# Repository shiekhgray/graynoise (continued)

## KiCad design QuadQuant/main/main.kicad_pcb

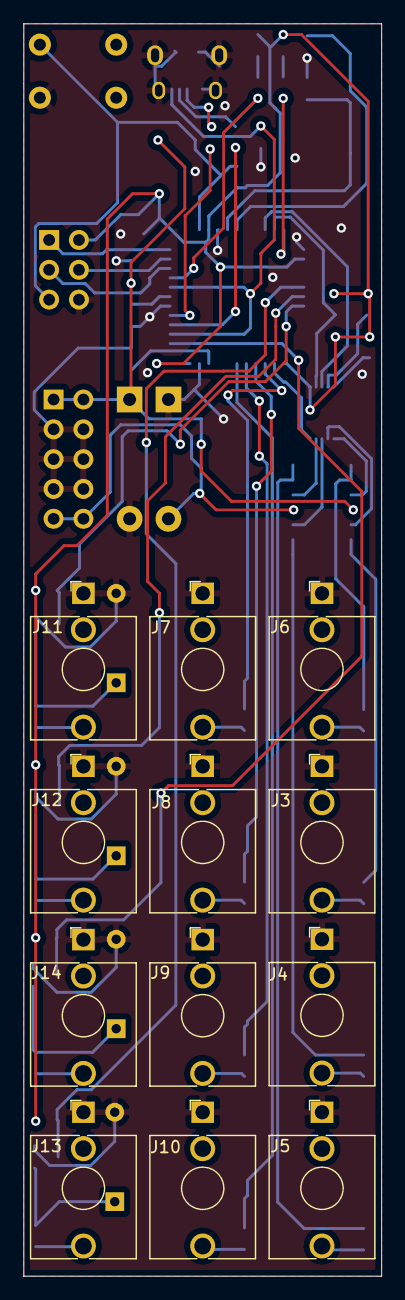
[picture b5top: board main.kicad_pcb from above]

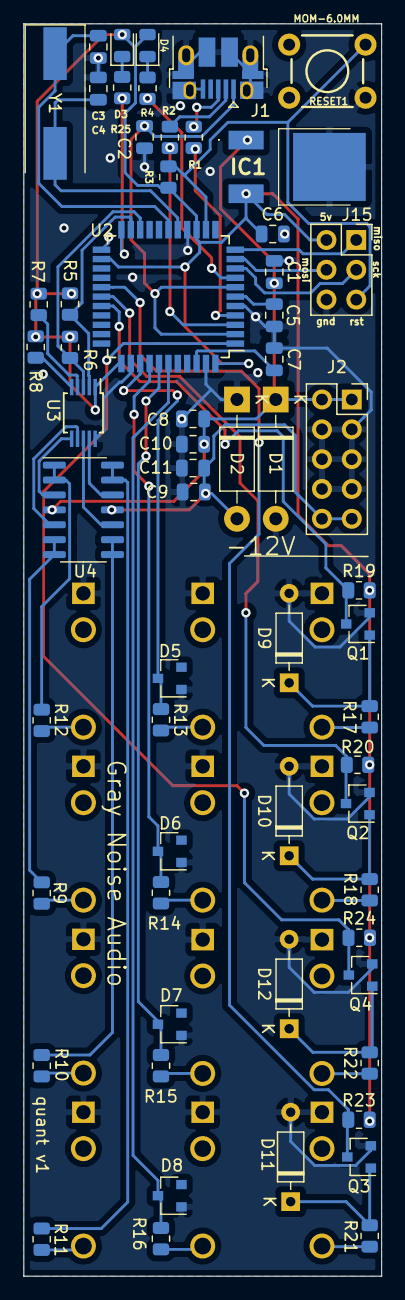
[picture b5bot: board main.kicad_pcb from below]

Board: 2 copper layers, 30.5 x 106.7 mm, 73 parts (61 on the bottom side), 57 nets.

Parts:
C1, C6, C7, C10, C11: 100n; C_0805_2012Metric
C2, C5: 1u; C_0805_2012Metric
C3, C4: 22p; C_0805_2012Metric
C8, C9: 10u; C_0805_2012Metric
D1, D2: 1N4001; D_DO-41_SOD81_P10.16mm_Horizontal
D3: LED_Green; LED_0805_2012Metric
D4: LED_Yellow; LED_0805_2012Metric
D5, D6, D7, D8: D_Zener_5v; D_SOT-23_ANK
D9, D10, D11, D12: 1N4148; D_DO-35_SOD27_P7.62mm_Horizontal
IC1: MC7805CDTRKG; MJD1221G
J1: USB_B_Mini; USB_Micro-B_Amphenol_10103594-0001LF_Horizontal
J2: Conn_02x05_Odd_Even; PinSocket_2x05_P2.54mm_Vertical
J3: OUT2; Jack_3.5mm_QingPu_WQP-PJ398SM_Vertical_CircularHoles
J4: OUT3; Jack_3.5mm_QingPu_WQP-PJ398SM_Vertical_CircularHoles
J5: OUT4; Jack_3.5mm_QingPu_WQP-PJ398SM_Vertical_CircularHoles
J6: OUT1; Jack_3.5mm_QingPu_WQP-PJ398SM_Vertical_CircularHoles
J7: CV1; Jack_3.5mm_QingPu_WQP-PJ398SM_Vertical_CircularHoles
J8: CV2; Jack_3.5mm_QingPu_WQP-PJ398SM_Vertical_CircularHoles
J9: CV3; Jack_3.5mm_QingPu_WQP-PJ398SM_Vertical_CircularHoles
J10: CV4; Jack_3.5mm_QingPu_WQP-PJ398SM_Vertical_CircularHoles
J11: Trig1; Jack_3.5mm_QingPu_WQP-PJ398SM_Vertical_CircularHoles
J12: Trig2; Jack_3.5mm_QingPu_WQP-PJ398SM_Vertical_CircularHoles
J13: Trig4; Jack_3.5mm_QingPu_WQP-PJ398SM_Vertical_CircularHoles
J14: Trig3; Jack_3.5mm_QingPu_WQP-PJ398SM_Vertical_CircularHoles
J15: Conn_02x03_Odd_Even; PinSocket_2x03_P2.54mm_Vertical
Q1, Q2, Q3, Q4: MMBT3904; SOT-23
R1, R2: 22; R_0805_2012Metric
R3: 10K; R_0805_2012Metric
R4, R9, R10, R11, R12, R25: 1K; R_0805_2012Metric
R5, R6, R7, R8, R13, R14, R15, R16, R17, R18, R19, R20, R21, R22, R23, R24: 100K; R_0805_2012Metric
RESET1: MOM-6.0MM; TACTILE_SWITCH_PTH_6.0MM
U2: ATmega32U4-AU; TQFP-44_10x10mm_P0.8mm
U3: MCP4728; MSOP-10_3x3mm_P0.5mm
U4: TL074; SOIC-14_3.9x8.7mm_P1.27mm
Y1: Crystal16mhz; Crystal_SMD_HC49-SD

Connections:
+5V: C6.1, D3.2, D4.2, IC1.3, J15.2, R3.1, R5.1, R6.1, R7.1, R8.1, R19.2, R20.2, R23.2, R24.2, U2.14, U2.24, U2.34, U2.44, U3.1
+12V: C1.2, C8.2, C10.2, D1.1, IC1.1, J2.1, J2.2, U4.4
-12V: C9.1, C11.1, D2.2, J2.9, J2.10, U4.11
CVA: D5.1, R13.1, U2.36
CVB: D6.1, R14.1, U2.37
CVC: D7.1, R15.1, U2.38
CVD: D8.1, R16.1, U2.39
GND: C1.1, C2.1, C3.2, C4.2, C5.1, C6.2, C7.1, C8.1, C9.2, C10.1, C11.2, D1.2, D2.1, D5.2, D6.2, D7.2, D8.2, D9.2, D10.2, D11.2, D12.2, IC1.2, J1.5, J1.6, J2.3, J2.4, J2.5, J2.6, J2.7, J2.8, J3.S, J4.S, J5.S, J6.S, J7.S, J8.S, J9.S, J10.S, J11.S, J12.S, J13.S, J14.S, J15.6, Q1.2, Q2.2, Q3.2, Q4.2, RESET1.1, U2.5, U2.15, U2.23, U2.35, U2.43, U3.10
LDAC: R7.2, U3.4
MISO: J15.1, U2.11
MOSI: J15.4, U2.10
unnamed: C3.1, U2.17, Y1.1
unnamed: C4.1, U2.16, Y1.2
unnamed: C5.2, U2.6
unnamed: C7.2, U2.42
unnamed: D3.1, R25.1
unnamed: D4.1, R4.1
unnamed: D9.1, Q1.1, R17.1
unnamed: D10.1, Q2.1, R18.1
unnamed: D11.1, Q3.1, R21.1
unnamed: D12.1, Q4.1, R22.1
unnamed: J1.2, R2.2
unnamed: J1.3, R1.2
unnamed: J3.T, R9.1
unnamed: J4.T, R10.1
unnamed: J5.T, R11.1
unnamed: J6.T, R12.1
unnamed: J7.T, R13.2
unnamed: J8.T, R14.2
unnamed: J9.T, R15.2
unnamed: J10.T, R16.2
unnamed: J11.T, R17.2
unnamed: J12.T, R18.2
unnamed: J13.T, R21.2
unnamed: J14.T, R22.2
unnamed: R1.1, U2.4
unnamed: R2.1, U2.3
unnamed: R4.2, U2.8
unnamed: R9.2, U4.6, U4.7
unnamed: R10.2, U4.8, U4.9
unnamed: R11.2, U4.13, U4.14
unnamed: R12.2, U4.1, U4.2
unnamed: R25.2, U2.22
RDY: R8.2, U3.5
RST: J15.5, R3.2, RESET1.3, U2.13
SCK: J15.3, U2.9
SCL: R5.2, U2.21, U3.2
SDA: R6.2, U2.20, U3.3
Trigger1: Q1.3, R19.1, U2.29
Trigger2: Q2.3, R20.1, U2.28
Trigger3: Q4.3, R24.1, U2.1
Trigger4: Q3.3, R23.1, U2.27
VOUTA: U3.6, U4.3
VOUTB: U3.7, U4.5
VOUTC: U3.8, U4.10
VOUTD: U3.9, U4.12
vbus: C2.2, J1.1, U2.2, U2.7

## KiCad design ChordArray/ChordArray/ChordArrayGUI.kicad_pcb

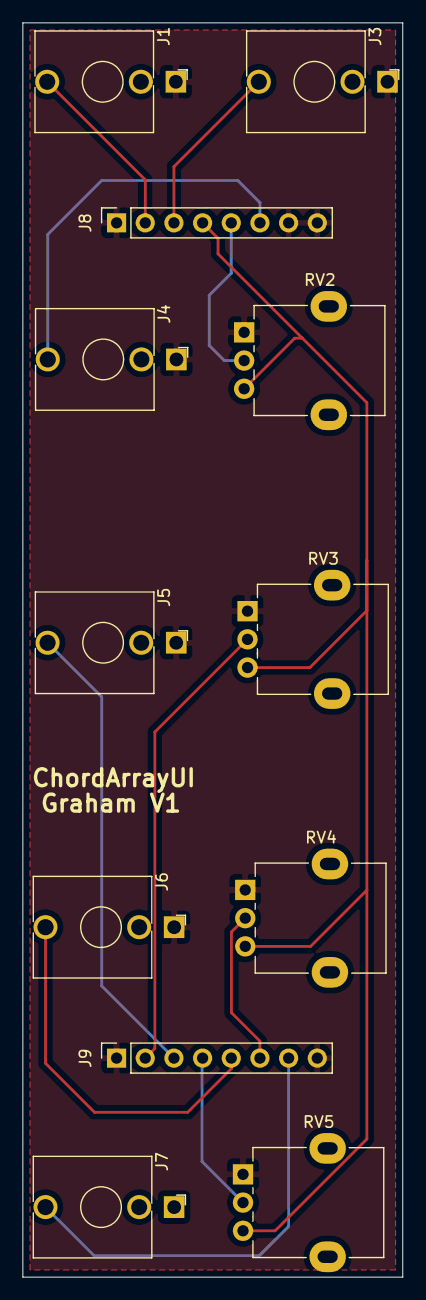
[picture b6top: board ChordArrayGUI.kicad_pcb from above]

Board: 2 copper layers, 33.7 x 111.1 mm, 12 parts (0 on the bottom side), 12 nets.

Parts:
J1: CV_IN; Jack_3.5mm_QingPu_WQP-PJ398SM_Vertical_CircularHoles
J3: BUFFERED_OUT; Jack_3.5mm_QingPu_WQP-PJ398SM_Vertical_CircularHoles
J4: OFFSET1; Jack_3.5mm_QingPu_WQP-PJ398SM_Vertical_CircularHoles
J5: OFFSET2; Jack_3.5mm_QingPu_WQP-PJ398SM_Vertical_CircularHoles
J6: OFFSET3; Jack_3.5mm_QingPu_WQP-PJ398SM_Vertical_CircularHoles
J7: OFFSET4; Jack_3.5mm_QingPu_WQP-PJ398SM_Vertical_CircularHoles
J8, J9: Conn_01x08_Male; PinSocket_1x08_P2.54mm_Vertical
RV2, RV3, RV4, RV5: 100K; Potentiometer_Alpha_RD901F-40-00D_Single_Vertical

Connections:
1V: J8.4, RV2.3, RV3.3, RV4.3, RV5.3
BUFFOUT: J3.T, J8.3
CVIN: J1.T, J8.2
GND: J1.S, J3.S, J4.S, J5.S, J6.S, J8.1, J8.7, J8.8, J9.1, J9.8, RV2.1, RV3.1, RV4.1, RV5.1
OFFP1: J8.5, RV2.2
OFFP2: J9.2, RV3.2
OFFP3: J9.4, RV5.2
OFFP4: J9.6, RV4.2
OFFS1: J4.T, J8.6
OFFS2: J5.T, J9.3
OFFS3: J6.T, J9.5
OFFS4: J7.T, J9.7

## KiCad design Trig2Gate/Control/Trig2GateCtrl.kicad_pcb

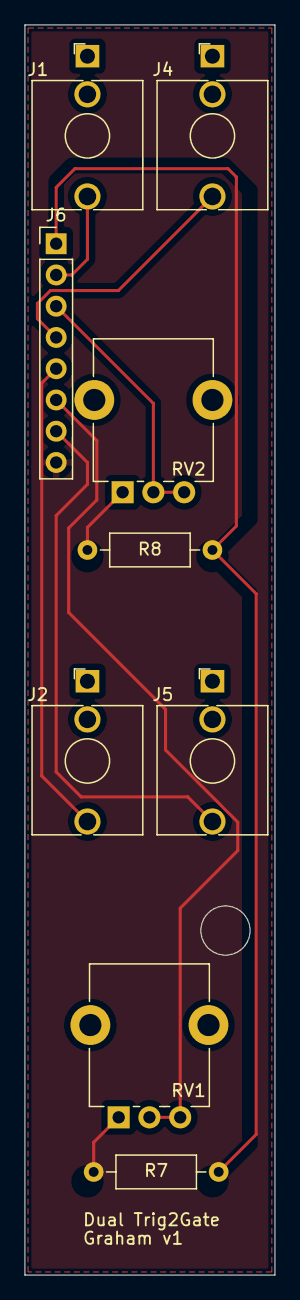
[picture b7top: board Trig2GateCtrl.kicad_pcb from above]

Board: 2 copper layers, 20.3 x 101.6 mm, 9 parts (0 on the bottom side), 9 nets.

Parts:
J1, J2, J4, J5: AudioJack2_Ground; Jack_3.5mm_QingPu_WQP-PJ398SM_Vertical_CircularHoles
J6: Conn_01x08_Male; PinHeader_1x08_P2.54mm_Vertical
R7, R8: 2K2; R_Axial_DIN0207_L6.3mm_D2.5mm_P10.16mm_Horizontal
RV1, RV2: 1M; Potentiometer_Alpha_RD901F-40-00D_Single_Vertical_CircularH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

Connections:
+12V: J6.1, R7.1, R8.1
G1: J4.T, J6.4
G2: J5.T, J6.7
unnamed: R7.2, RV1.1
unnamed: R8.2, RV2.1
T1: J1.T, J6.2
T2: J2.T, J6.5
V1: J6.3, RV2.2, RV2.3
V2: J6.6, RV1.2, RV1.3

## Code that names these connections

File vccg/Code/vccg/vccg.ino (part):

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int melody;           //quantized melody note

int noteCV = 0;         //CV of note to quantize to scale;
int chordCV = 0;        //CV of the chord. Should scale 0-5v, chords I->VII
int octaveCV = 0;       //CV of the octave. Should scale 0-5v, 1v/octave

int keyUp = 0;          //Press to increment key, i.e. from C to C#
int keyUpPrevious = 0;
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int clockCV = 0;        //Whether the module has received a clock signal
int clockCVPrevious = 1;

int melodyClock = 0;
int melodyClockPrevious = 1;

int isMinor = 0;          //Switch to toggle major/minor
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  Serial.begin(115200);
  Serial.println(F("Unit On!"));

  pinMode(5, INPUT); //chordClock
  pinMode(6, INPUT); //melodyClock
  pinMode(7, INPUT); //keyUp
  pinMode(8, INPUT); //keyDown
  pinMode(9, INPUT); //isMinor
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//Based on whatever CV we see, pick an octave between 0 and 4
//1024 total DAC space
int octaveSelect(int octaveCV) {
  int octave = 0;

  if (octaveCV >= 0 && octaveCV < 205) {
    octave = 0;
  } else if (octaveCV >= 206 && octaveCV < 410) {
    octave = 1;
  } else if (octaveCV >= 411 && octaveCV < 615) {
    octave = 2;
  } else if (octaveCV >= 616 && octaveCV < 820) {
    octave = 3;
  } else {
    octave = 4;
  }

  return octave;
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//Based on whatever CV we see, pick a chord betwen I and VII (1 and 7)
//1024 total DAC space
int chordSelect(int chordCV) {
  int chord = 0;

  if (chordCV >= 0 && chordCV < 146) {
    chord = 1;
  } else if (chordCV >= 147 && chordCV < 294) {
    chord = 2;
  } else if (chordCV >= 295 && chordCV < 441) {
    chord = 3;
  } else if (chordCV >= 442 && chordCV < 588) {
    chord = 4;
  } else if (chordCV >= 589 && chordCV < 735) {
    chord = 5;
  } else if (chordCV >= 736 && chordCV < 882) {
    chord = 6;
  } else {
    chord = 7;
  }

  return chord;
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
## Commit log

2021-04-26 adding 4mixer
2021-04-26 adding offset attenuverter... even though the PCB is screwed up
2021-04-26 updating readme for the 2 modules I added
2021-04-26 updating readme
2021-04-26 let's let folks know that I garbled the pcbnew file here
2021-04-26 Update README.md
    list eurorack module width for 4mixer
2021-04-28 4mixer faceplate and gerbers
    Tinkering with the mixer faceplate, adding gerbers and so on.
2021-04-28 organizing the mixer better
    good lord kicad makes a mess
2021-04-28 organizing offset attenuverter
    kicad cleanup
2021-04-28 create mixer fp-info-cache
2021-04-28 Back from the fab.... modules are actually 5" + 1/16" tall. Not flat 5".
    Rework to fit. Also, the text on these came out really tiny, increase
    where possible. Also add gerbers
2021-04-28 This faceplate was also incredibly wrong.
2021-04-28 saving the fixes for the offsetting attenuator
2021-04-28 saving the faceplate fixes
2021-05-05 Adding a quick note about the upcoming white noise and chaos source
2021-05-05 that grammar was terrible. This is better I hope
2021-05-05 multi pcb layouts are gross, but here we are.
2021-05-05 avalanche wip
    Add some avalanche stuff
2021-05-09 First stab at a quad quantizer
    WIP
2021-05-09 Avalanche cleanup
2021-05-09 cleanup
2021-05-10 Adding programming headers
    Also starting in on a PCB layout. My smd work is so fugly right now.
2021-05-11 Hmm. Feeling stuck
    Saving progress so I can get back here if necessary
2021-05-13 quantizer first pass at routing
    Much better with a hair more breathing room. Also I think I had the usb flipped backwards. Fixed.
2021-06-24 fixing drill holes, adding logo
2021-06-24 4mixer cleanup and logo test
2021-09-19 Yeet some rough code into here
2021-09-19 arduino has ideas about where things need to be.
2021-09-20 Slammed out the hardware design for the brains. Needs some cleanup. WIP.
    Noticed that it could use a bit of a dramatic redesign with regards to
    where the potentiometers are. They're very close to the edge of the
    board, which might make them ergonomically hard to use. Given that
    there's a lot of extra space I thought I'd stop here and try again in
    another branch. Hooray for git
2021-09-20 add ic2 pull up resistors. Rewire to 10HP.
2021-09-22 add some custom key generation. Doing this on the fly preserves 60% of
    the memory. There may be a way to save this data in functions that only
    get called once in a while or something instead of saving all the key
    data in global variables.
2021-09-23 Add info to output screen. Tinker with methods to save SRAM
2021-09-23 get chor case correct, hopefully.
2021-09-23 Yeet all them grb files into place
2021-09-23 afsdfasd
2021-10-01 Running out of memory on the atmega328.
    Weird behavior as a result as variables keep getting overwritten by
    other stuff
2021-10-01 VCCG WORKING.
    chord cv works
    octave cv works
    minor/major toggle works
    screen shows correct information
    3 chord outputs are correct
    TODO:
2021-10-01 VCCG Cleanup debugging pieces, enbiggening the display
2021-10-02 vccg adjust display sizes so that things are always readable
2021-10-02 Strip variables out of functions. Use limited globals instead.
    Also straighten up the display of the chords
2021-10-02 When the key changes, actually change the values of the key
    Also recompute the key if the key changes from major to minor or vice
    versa
2021-10-03 3 features:
    clocking
    autoclocking
    melody quantization
2021-10-03 Do some work to speed up the output...It's still a bit slow
2021-11-14 vccg updates and gbrs and stuff
2022-01-16 first swing at micropython build for the raspberry pi pico board
2022-02-20 wip adafruit style
2022-03-06 testing a transistor vca to build into a wild mixer
2022-03-06 quick gcode test
2022-03-10 switch to mbt3904 double transistor 2n3904 dual package
2022-03-10 yeet
    3904 gcode
2022-03-25 VCA state working with jelly bean 2n3904 transistors
2022-03-25 mini transistor success!
2022-04-03 WIP working towards a mixer
    2 channels laid out with 207 resistors and TL074s. I need to move to TL072s and monolithic transistors in a few places for saner routing
2022-04-04 WIP 0805 TL072 dual channel
2022-04-05 WIP 0805 detangle
2022-04-16 4/6 channels, 4 routed
2022-04-17 mixer WIP, 8 channels, more or less
2022-04-18 WIP
    BUT! all routes complete for pan, mix, and VCA bank
2022-07-20 bigMix
2022-07-20 lost vccg C file
2022-10-19 Final pass
    note, at least USB doesn't work at this state. I don't know what else
    doesn't work. 3v3 power works, I can't speak to the rest.
2022-10-29 updating to use pi pico, all parts on back
2022-10-30 first pass at BOM/Centroid file
    todo:
    * rotations incorrect.
    * missing MCP6002 chips because JLCPCB is out
2022-11-06 fix to manufacturing files
2022-11-06 adding a diode to protect from usb5v.
    rotating oled output pins to line up with oled module
2023-02-12 Micropython rework with encoder WIP
2023-02-12 removing old arduino code
2023-02-12 add hex inverter to clean up nasty encoder output
2023-06-14 Adding Molly's shiny new faceplate design
2023-06-14 vccg 1.4 manufacturing files
2023-06-14 VCCG Version 1.4
    Features:
    * New hex inverter signal cleanup on the rotary encoder pins
    * Layout updates
    * MCP6002 footprint changes to match JLCPCB parts availability
    * Inductor footprint changes to match JLCPCB parts availability
2023-06-14 tinkering with getting menu items
2023-06-14 updating with actual gerbers instead of DXF files (whoops)
2023-06-14 massive cleanup
2023-06-14 Gerbers, not DXF files
2023-06-14 Adding my synth footprints so I can have them between working computers
2024-03-17 I made a revision using the raspbery pi pico and a rotary encoder
    but the combination of the rotary encoder interrupts and the precise
    timing needed to talk to both I2C endpoints means that I don't have the
    coding chops to sort out how to make this not crash, so I'm going to put
    a pin in this design and rework to 4 mom buttons instead
2024-03-18 Rebuild with 4 mom buttons instead of rotary encoder
